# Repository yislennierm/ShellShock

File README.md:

This is the main repo for the mister shell shock console

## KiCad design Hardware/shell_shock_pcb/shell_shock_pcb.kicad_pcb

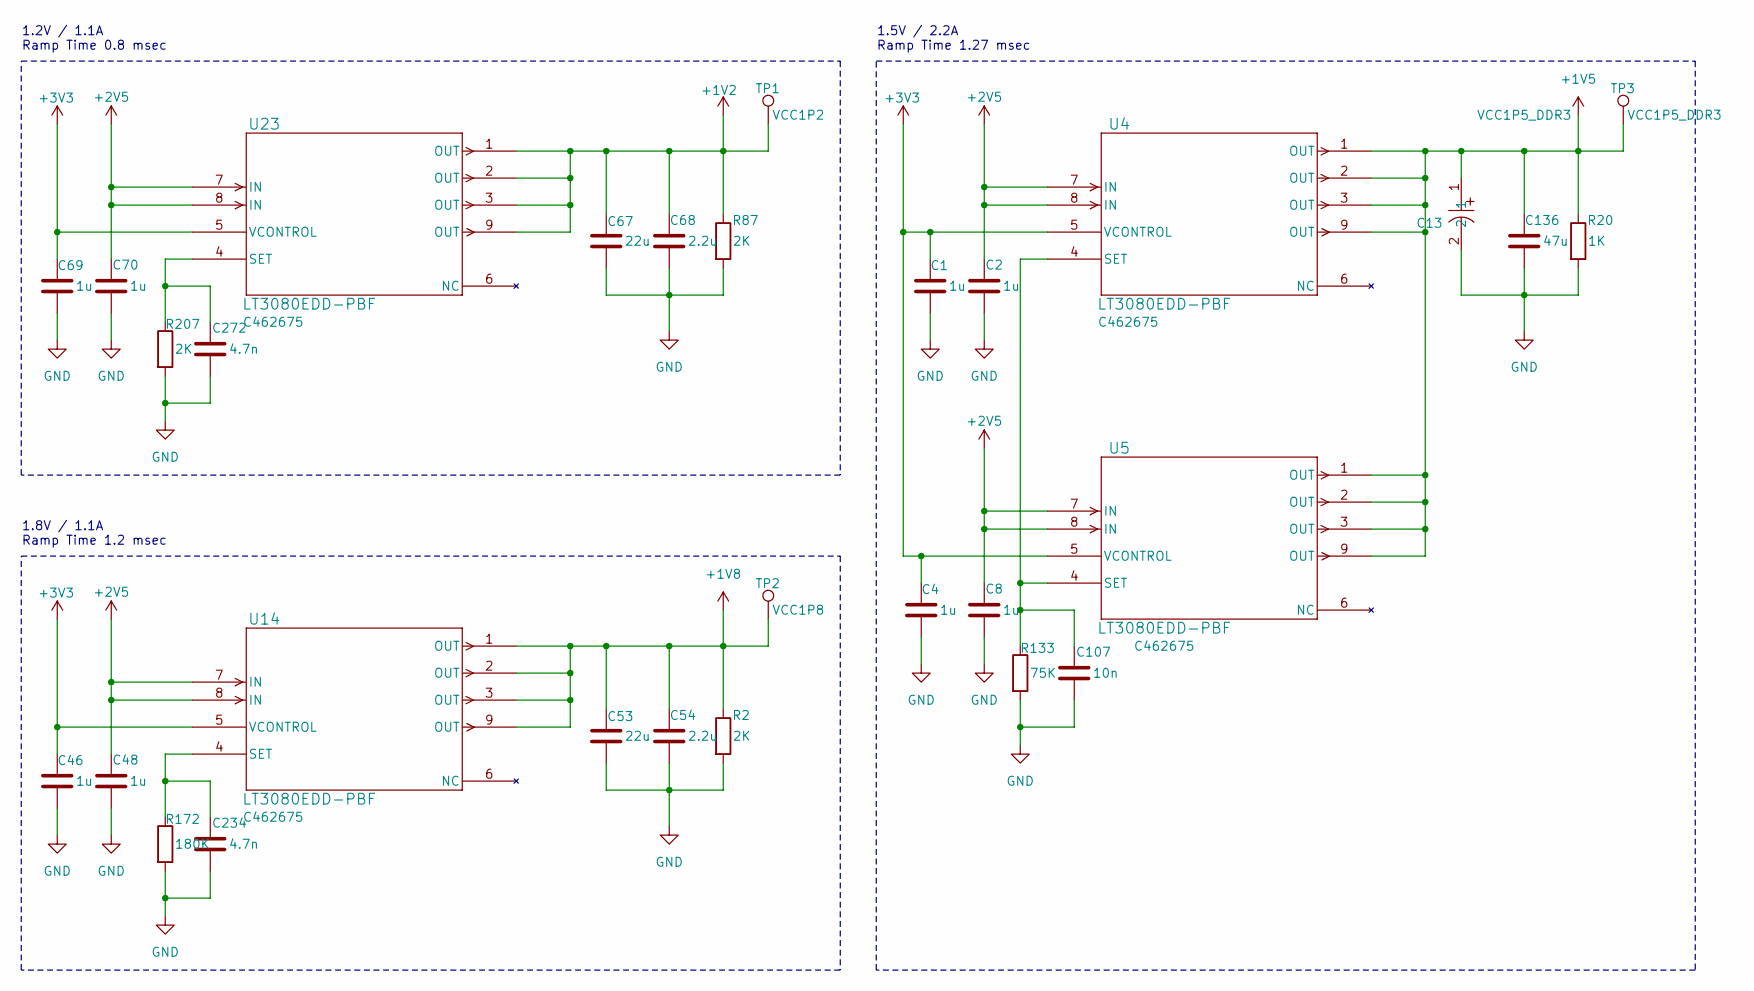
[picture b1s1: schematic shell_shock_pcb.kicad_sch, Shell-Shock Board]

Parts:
C1, C2, C4, C8, C46, C48: 1u; C_0402_1005Metric; LCSC C14445
C13: T520A107M006ATE070; CAP-SMD_L3.2-W1.6; LCSC Part C561794
C53: 22u; C_0805_2012Metric; LCSC C602037
C54: 2.2u; C_0402_1005Metric; LCSC C170151
C67: 22u; C_0805_2012Metric
C68: 2.2u; C_0402_1005Metric
C69, C70: 1u; C_0402_1005Metric
C107: 10n; C_0402_1005Metric; LCSC C15195
C136: 47u; C_0805_2012Metric; LCSC C16780
C234: 4.7n; C_0402_1005Metric; LCSC C106208
C272: 4.7n; C_0402_1005Metric
R2, R87: 2K; R_0402_1005Metric; LCSC C2909344
R20: 1K; R_0402_1005Metric; LCSC C106235
R133: 75K; R_0402_1005Metric; LCSC C2909383
R172: 180K; R_0402_1005Metric; LCSC C138046
R207: 2K; R_0402_1005Metric
TP1: VCC1P2; TestPoint_Pad_D1.0mm
TP2: VCC1P8; TestPoint_Pad_D1.0mm
TP3: VCC1P5_DDR3; TestPoint_Pad_D1.0mm
U4, U5, U14, U23: LT3080EDD-PBF; DFN-8_L3.0-W3.0-P0.50-BL-EP; LCSC C462675

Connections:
+1V2: C67.1, C68.1, R87.1, TP1.1, U23.1 (OUT), U23.2 (OUT), U23.3 (OUT), U23.9 (OUT)
+1V5: C13.1, C136.1, R20.1, TP3.1, U4.1 (OUT), U4.2 (OUT), U4.3 (OUT), U4.9 (OUT), U5.1 (OUT), U5.2 (OUT), U5.3 (OUT), U5.9 (OUT)
+1V8: C53.1, C54.1, R2.1, TP2.1, U14.1 (OUT), U14.2 (OUT), U14.3 (OUT), U14.9 (OUT)
+2V5: C2.1, C8.1, C48.1, C70.1, U4.7 (IN), U4.8 (IN), U5.7 (IN), U5.8 (IN), U14.7 (IN), U14.8 (IN), U23.7 (IN), U23.8 (IN)
+3V3: C1.1, C4.1, C46.1, C69.1, U4.5 (VCONTROL), U5.5 (VCONTROL), U14.5 (VCONTROL), U23.5 (VCONTROL)
GND: C1.2, C2.2, C4.2, C8.2, C13.2, C46.2, C48.2, C53.2, C54.2, C67.2, C68.2, C69.2, C70.2, C107.2, C136.2, C234.2, C272.2, R2.2, R20.2, R87.2, R133.2, R172.2, R207.2
unnamed: C107.1, R133.1, U4.4 (SET), U5.4 (SET)
unnamed: C234.1, R172.1, U14.4 (SET)
unnamed: C272.1, R207.1, U23.4 (SET)

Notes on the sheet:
1.2V / 1.1A Ramp Time 0.8 msec
1.8V / 1.1A Ramp Time 1.2 msec
1.5V / 2.2A Ramp Time 1.27 msec

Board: 2 copper layers, 30 parts (0 on the bottom side), 9 nets, no tracks yet.

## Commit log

2025-10-30 added test
2026-02-08 Add initial README for mister shell shock console
2026-02-08 Update folder structure
2026-02-08 Created datasheets folder
2026-02-08 Added hardware tools
2026-02-08 sketch pcb for LT3080 ps
